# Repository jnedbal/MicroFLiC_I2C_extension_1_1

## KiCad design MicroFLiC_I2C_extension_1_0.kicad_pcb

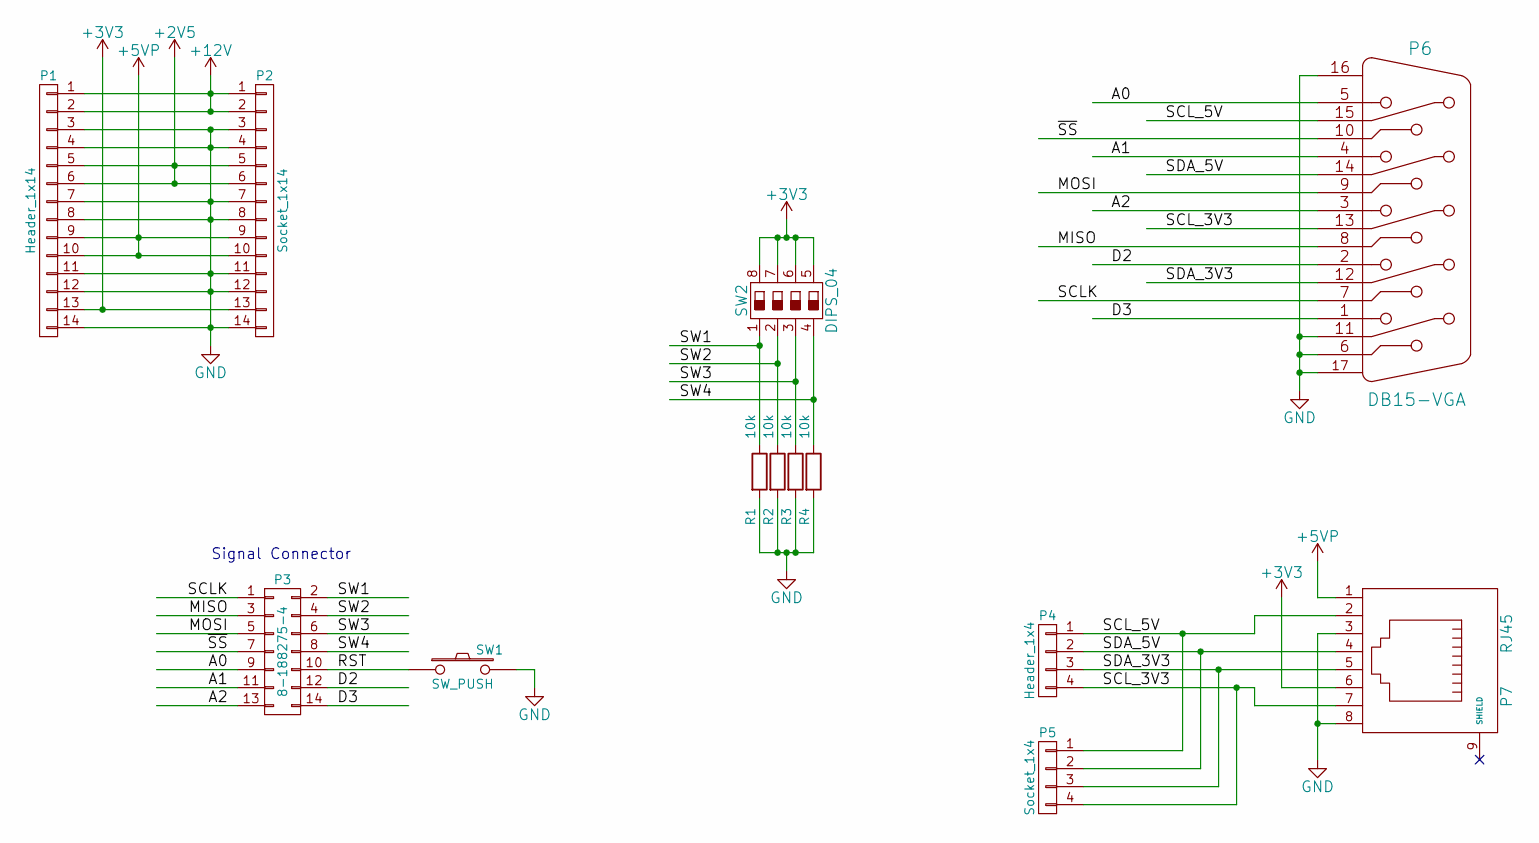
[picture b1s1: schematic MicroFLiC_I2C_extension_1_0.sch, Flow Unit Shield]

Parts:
P1: Header_1x14; Pin_Header_Straight_1x14; Part Number HTSW-114-15-G-S
P2: Socket_1x14; ESQ-114-33-G-S; Part Number ESQ-114-33-G-S
P3: 8-188275-4; 1-188275-4; Part Number 8-188275-4
P4: Header_1x4; Pin_Header_Straight_1x04; Part Number HTSW-104-15-G-S
P5: Socket_1x4; ESQ-104-33-G-S; Part Number ESQ-104-33-G-S
P6: DB15-VGA; dsub15; Part Number L77HDE15SD1CH4F
P7: RJ45; Part Number 95501-2881
R1, R2, R3, R4: 10k; R_0805; Part Number MCMR08X1002FTL
SW1: SW_PUSH; tactileSwitchRA; Part Number MCDTSA6-5N
SW2: DIPS_04; DIP4RA; Part Number MCDA04

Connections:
+2V5: P1.5, P1.6, P2.5, P2.6
+3V3: P1.13, P2.13, P7.6, SW2.5, SW2.6, SW2.7, SW2.8
+5VP: P1.9, P1.10, P2.9, P2.10, P7.1
+12V: P1.1, P1.2, P2.1, P2.2
/A0: P3.9, P6.5
/A1: P3.11, P6.4
/A2: P3.13, P6.3
/D2: P3.12, P6.2
/D3: P3.14, P6.1
/MISO: P3.3, P6.8
/MOSI: P3.5, P6.9
/RST: P3.10, SW1.1
/SCLK: P3.1, P6.7
/SCL_3V3: P4.4, P5.4, P6.13, P7.7
/SCL_5V: P4.1, P5.1, P6.15, P7.2
/SDA_3V3: P4.3, P5.3, P6.12, P7.5
/SDA_5V: P4.2, P5.2, P6.14, P7.4
/SW1: P3.2, R1.1, SW2.1
/SW2: P3.4, R2.1, SW2.2
/SW3: P3.6, R3.1, SW2.3
/SW4: P3.8, R4.1, SW2.4
/~SS: P3.7, P6.10
GND: P1.3, P1.4, P1.7, P1.8, P1.11, P1.12, P1.14, P2.3, P2.4, P2.7, P2.8, P2.11, P2.12, P2.14, P6.6, P6.11 (P111), P6.16 (SHIELD), P6.17 (SHIELD), P7.3, P7.8, R1.2, R2.2, R3.2, R4.2, SW1.2

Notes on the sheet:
Signal Connector

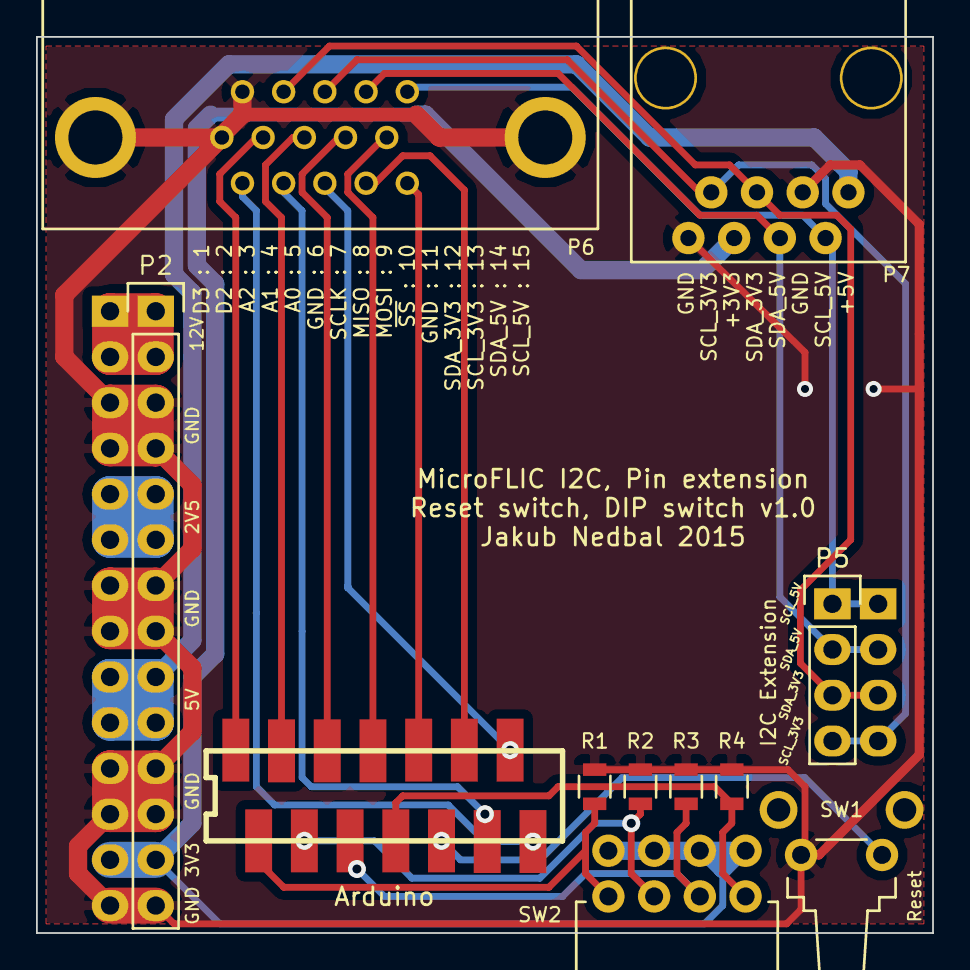
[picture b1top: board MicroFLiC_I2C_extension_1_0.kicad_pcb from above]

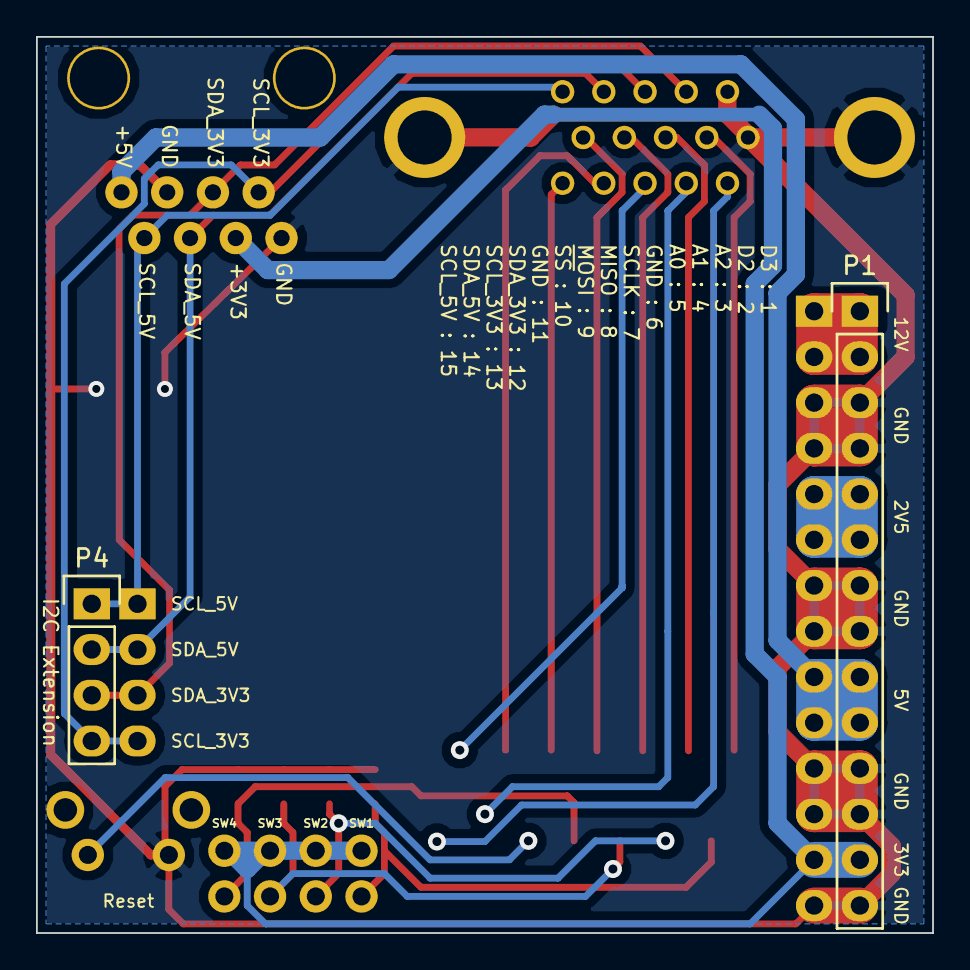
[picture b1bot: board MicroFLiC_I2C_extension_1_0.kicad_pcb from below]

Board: 2 copper layers, 49.8 x 49.8 mm, 13 parts (2 on the bottom side), 23 nets.

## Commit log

2016-01-06 Final production board v1.0
2016-02-11 Fixed part numbers
2016-02-11 Started version 1.1, renamed files.
2016-02-11 Filled in component details, update board to v1.1
2016-02-26 Fixed connector descriptions
2016-02-28 Minor part description changes
